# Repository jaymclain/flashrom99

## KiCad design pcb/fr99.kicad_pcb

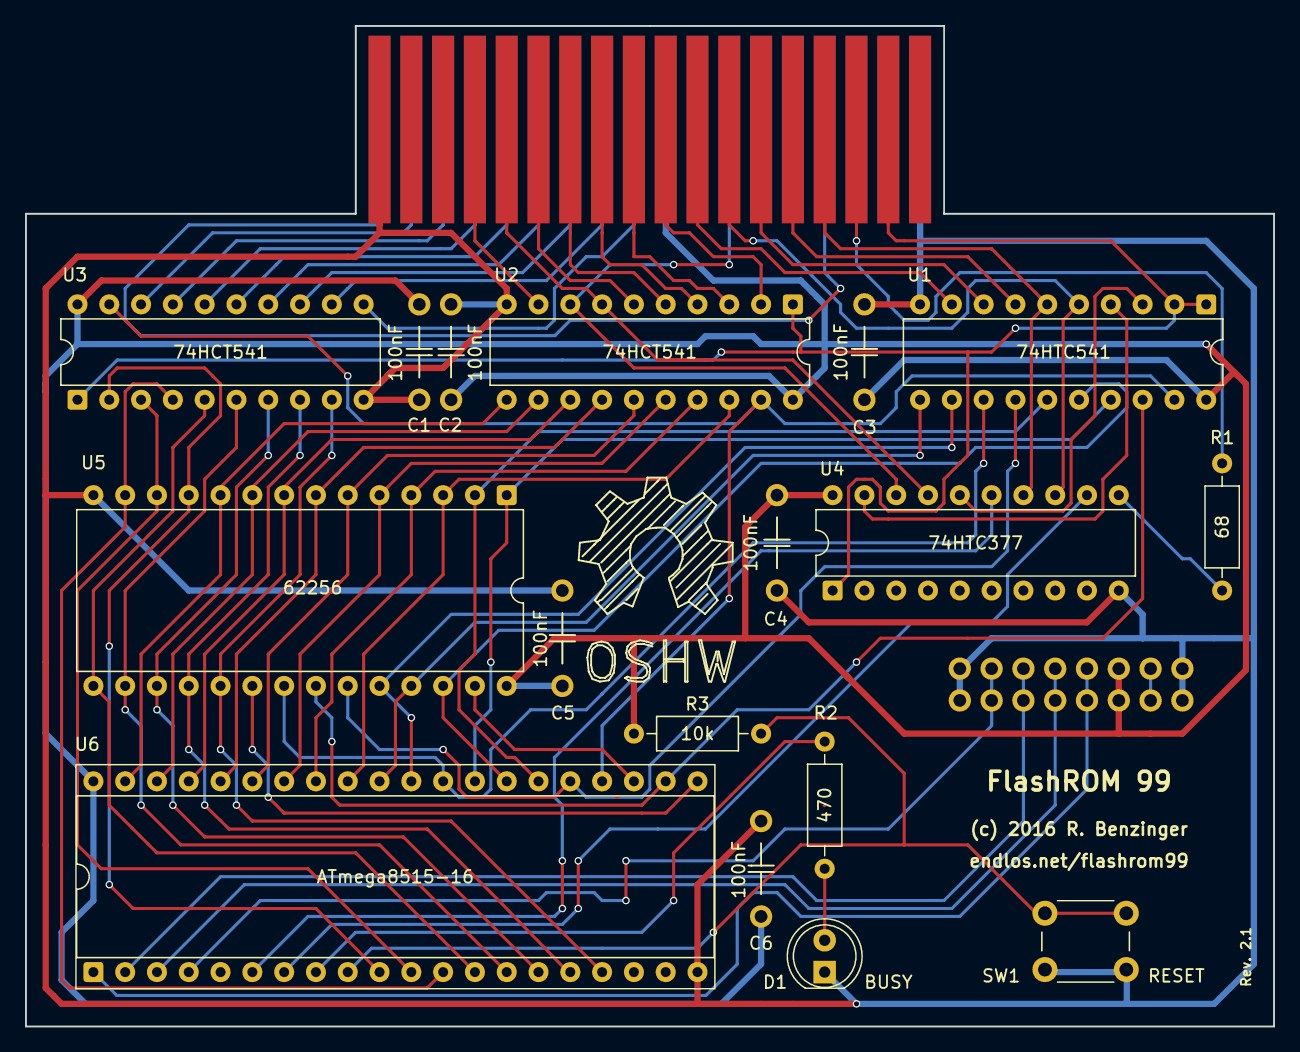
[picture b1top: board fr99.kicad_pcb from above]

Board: 2 copper layers, 99.7 x 79.9 mm, 19 parts (1 on the bottom side), 65 nets.

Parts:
C1, C2, C3, C4, C5, C6: 100nF; C_C
D1: BUSY; LED_D5.0mm
M1: SD; SD_MODULE
P1: CONN_02X18; BUS_CART
R1: 68; R_Axial_DIN0207_L6.3mm_D2.5mm_P10.16mm_Horizontal
R2: 470; R_Axial_DIN0207_L6.3mm_D2.5mm_P10.16mm_Horizontal
R3: 10k; R_Axial_DIN0207_L6.3mm_D2.5mm_P10.16mm_Horizontal
SW1: RESET; SW_PUSH_6mm_H5mm
U1: 74HTC541; DIP-20_W7.62mm
U2, U3: 74HCT541; DIP-20_W7.62mm
U4: 74HTC377; DIP-20_W7.62mm
U5: 62256; DIP-28_W15.24mm
U6: ATmega8515-16; DIP-40_W15.24mm_Socket

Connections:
+5V: C1.2, C2.2, C3.2, C4.2, C5.2, C6.2, M1.6, P1.19, R3.1, U1.20, U2.20, U3.20, U4.20, U5.28, U6.40
/A0: U2.11, U5.10, U6.39
/A1: U2.12, U5.9, U6.38
/A2: U2.13, U5.8, U6.37
/A3: U2.14, U5.7, U6.36
/A4: U2.15, U5.6, U6.35
/A5: U2.16, U5.5, U6.34
/A6: U2.17, U5.4, U6.33
/A7: U2.18, U5.3, U6.32
/A8: U1.11, U5.25, U6.31
/A9: U1.12, U5.24, U6.30
/A10: U1.13, U5.21, U6.29
/A11: U1.14, U5.23, U6.25
/A12: U1.15, U5.2, U6.26
/A13: U1.16, U5.26, U6.27
/A14: U1.17, U5.1, U6.28
/D0: U3.2, U5.11, U6.10
/D1: U3.3, U5.12, U6.11
/D2: U3.4, U5.13, U6.12
/D3: U3.5, U5.15, U6.13
/D4: U3.6, U5.16, U6.14
/D5: U3.7, U5.17, U6.15
/D6: U3.8, U5.18, U6.16
/D7: U3.9, U5.19, U6.17
BUSE: U1.19, U2.19, U3.19, U6.24
GND: C1.1, C2.1, C3.1, C4.1, C5.1, C6.1, D1.1, M1.1, M1.8, P1.2, P1.35, SW1.1, U1.10, U2.10, U3.10, U4.10, U5.14, U6.20
unnamed: R1.1, U4.11
unnamed: D1.2, R2.1
unnamed: M1.2, U6.4
unnamed: M1.3, U6.2
unnamed: M1.4, U6.3
unnamed: M1.5, U6.1
unnamed: P1.1, P1.29
unnamed: P1.3, U3.18
unnamed: P1.5, U3.17
unnamed: P1.7, U3.16
unnamed: P1.8, U2.9
unnamed: P1.9, U3.15
unnamed: P1.10, U2.7, U4.17
unnamed: P1.11, U3.14
unnamed: P1.12, U2.6
unnamed: P1.13, U3.13
unnamed: P1.14, U2.5
unnamed: P1.15, U3.12
unnamed: P1.16, U2.4
unnamed: P1.17, U3.11
unnamed: P1.18, U2.3
unnamed: P1.20, U2.2
unnamed: P1.22, U1.9
unnamed: P1.23, U2.8, U4.18
unnamed: P1.24, U1.5, U4.13
unnamed: P1.26, U1.8
unnamed: P1.28, U1.7
unnamed: P1.30, U1.6, U4.14
unnamed: P1.32, R1.2
unnamed: R2.2, U6.8
unnamed: R3.2, SW1.2, U6.9
unnamed: U1.3, U4.16
unnamed: U1.4, U4.19
unnamed: U1.18, U5.22, U6.22
unnamed: U4.12, U6.7
unnamed: U4.15, U6.6
unnamed: U5.20, U6.21
unnamed: U5.27, U6.23
ROMS: P1.34, U1.1, U1.2, U2.1, U3.1, U4.1

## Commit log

2025-05-08 Initial conversion to KiCad 9
2025-05-09 Cleanup footprints and library links
2025-05-09 Update schematic date and revision

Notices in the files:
pcb/fr99.kicad_pcb:
Copyright (c) 2016 Ralph Benzinger
Released as Open Source Hardware under CERN OHL 1.2 and GNU GPL 3 licenses
(c) 2016 R. Benzinger
